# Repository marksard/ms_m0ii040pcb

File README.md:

# m0ii040 PCB

ms_m0ii040PCB is a dedicated PCB for m0ii040 produced by [yohewi](https://github.com/yohewi).  
This keyboard has two different PCBs with different layouts.  

# Completed example
Row staggered layout  

Treadstone layout  

# Layout
Row staggered layout  

Treadstone layout  

# Support software

QMK Firmware  
https://github.com/marksard/qmk_firmware/tree/own_build/keyboards/marksard/m0ii040pcb

# Build guide

https://github.com/marksard/ms_m0ii040pcb/blob/main/documentes/buildguide.md

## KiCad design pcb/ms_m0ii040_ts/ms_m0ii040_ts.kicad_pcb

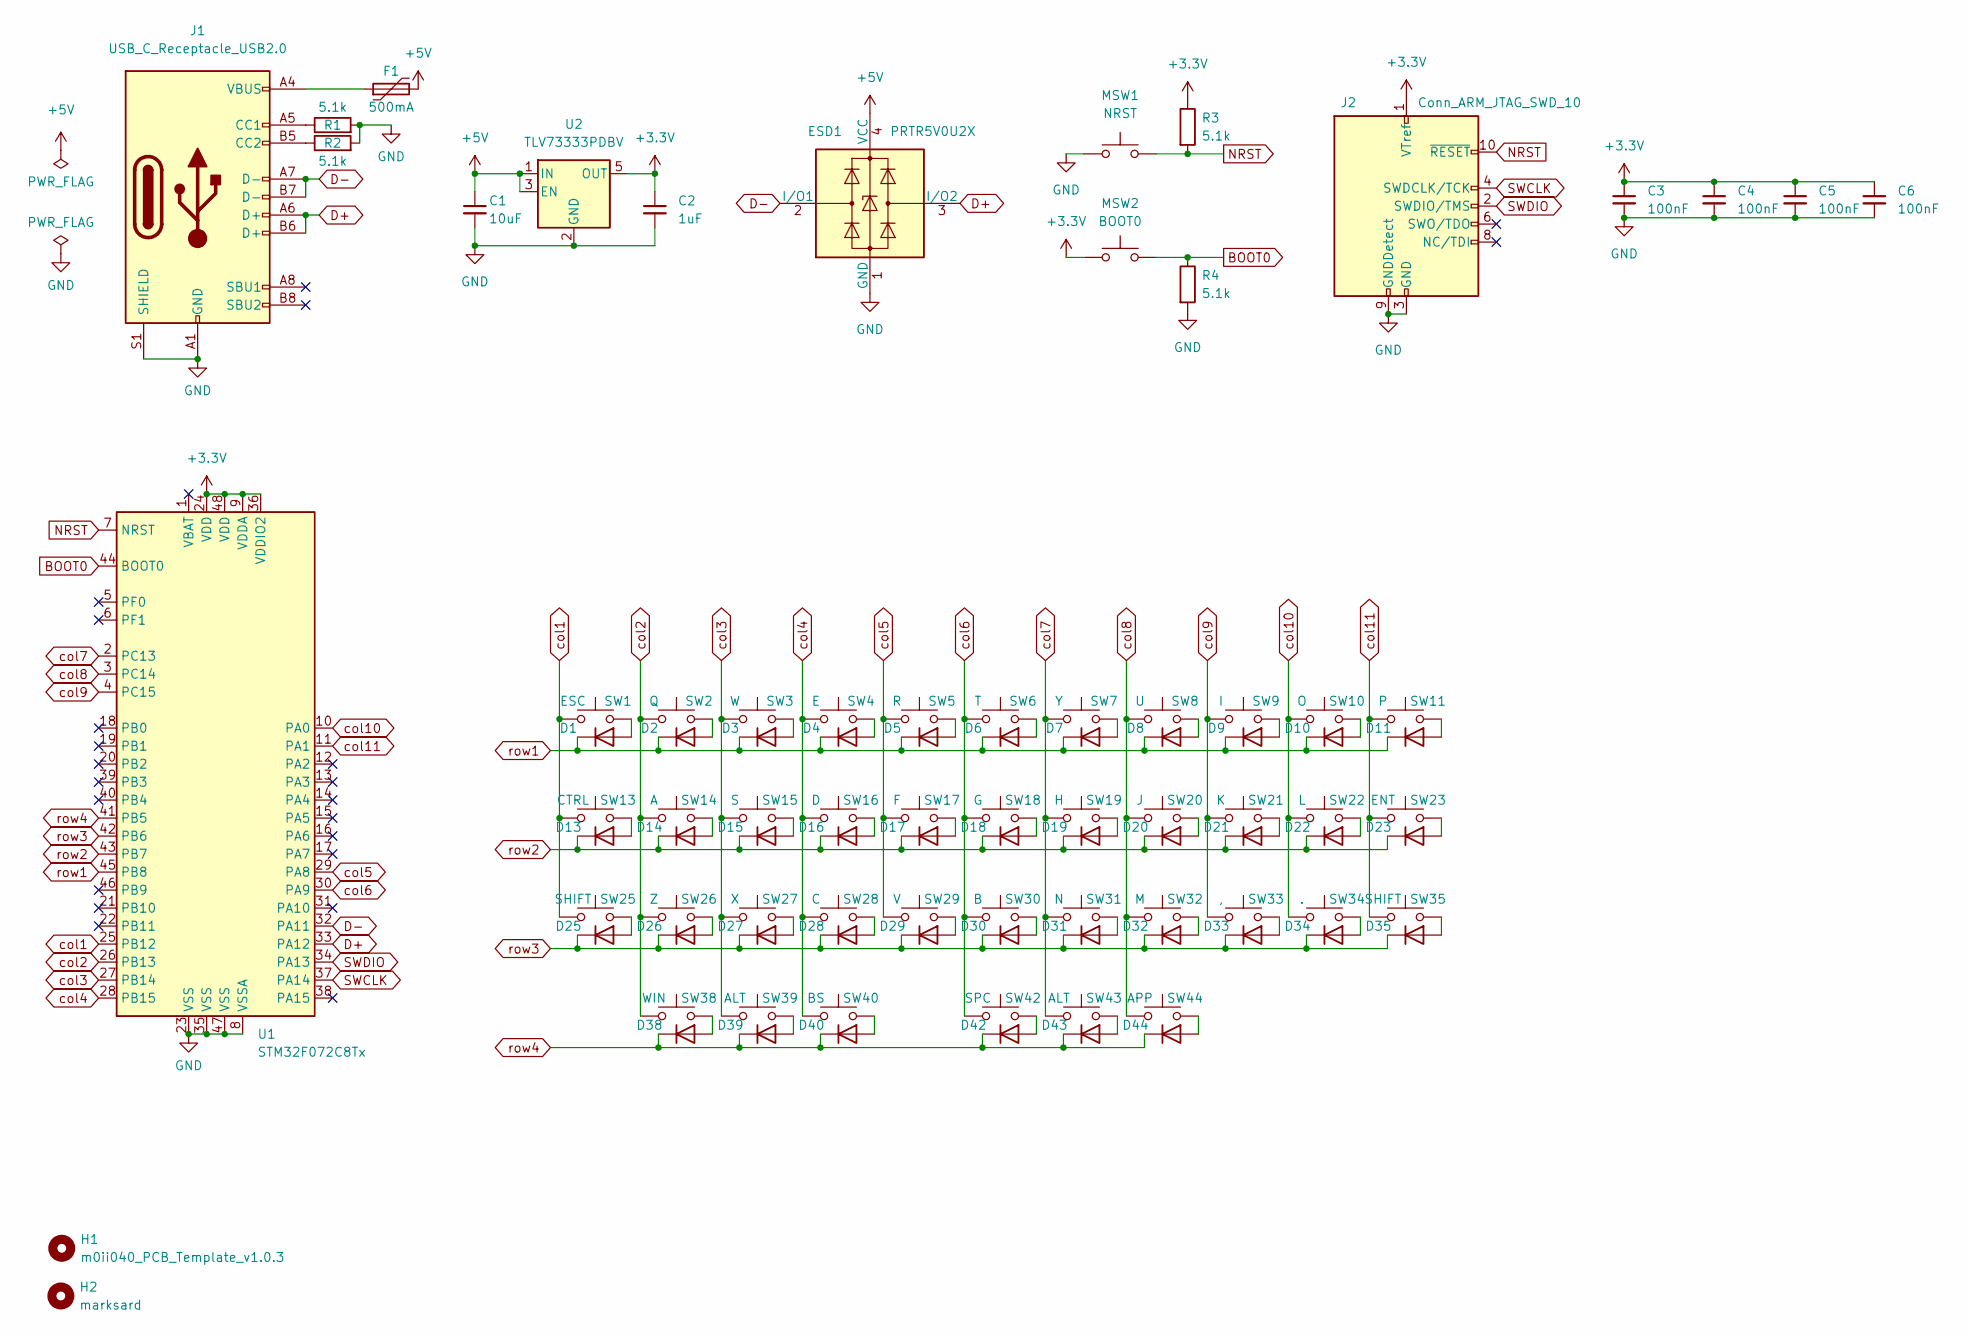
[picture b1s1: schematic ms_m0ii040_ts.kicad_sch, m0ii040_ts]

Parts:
C1: 10uF; C_0603_1608Metric
C2: 1uF; C_0402_1005Metric
C3, C4, C5, C6: 100nF; C_0402_1005Metric
D1, D2, D3, D4, D5, D6, D7, D8, D9, D10, D11, D13, D14, D15, D16, D17, D18, D19, D20, D21, D22, D23, D25, D26, D27, D28, D29, D30, D31, D32, D33, D34, D35, D38, D39, D40, D42, D43, D44: D; D_SOD-123; LCSC C81598
ESD1: PRTR5V0U2X; SOT-143; LCSC C12333
F1: 500mA; Fuse_0805_2012Metric; LCSC C261942
H1: m0ii040_PCB_Template_v1.0.3
H2: marksard; marksard_logo
J1: USB_C_Receptacle_USB2.0; HRO-TYPE-C-31-M-12-Assembly; LCSC C165948
J2: Conn_ARM_JTAG_SWD_10; PinHeader_2x06_P1.00mm_Vertical
MSW1: NRST; TVBP06-B043CB
MSW2: BOOT0; TVBP06-B043CB
R1, R2: 5.1k; R_0603_1608Metric
R3, R4: 5.1k; R_0402_1005Metric
SW1: ESC; MX-Hotswap-1U
SW2: Q; MX-Hotswap-1U
SW3: W; MX-Hotswap-1U
SW4: E; MX-Hotswap-1U
SW5: R; MX-Hotswap-1U
SW6: T; MX-Hotswap-1U
SW7: Y; MX-Hotswap-1U
SW8: U; MX-Hotswap-1U
SW9: I; MX-Hotswap-1U
SW10: O; MX-Hotswap-1U
SW11: P; MX-Hotswap-1U
SW13: CTRL; MX-Hotswap-1.25U
SW14: A; MX-Hotswap-1U
SW15: S; MX-Hotswap-1U
SW16: D; MX-Hotswap-1U
SW17: F; MX-Hotswap-1U
SW18: G; MX-Hotswap-1U
SW19: H; MX-Hotswap-1U
SW20: J; MX-Hotswap-1U
SW21: K; MX-Hotswap-1U
SW22: L; MX-Hotswap-1U
SW23: ENT; MX-Hotswap-1.75U
SW25: SHIFT; MX-Hotswap-1U
SW26: Z; MX-Hotswap-1U
SW27: X; MX-Hotswap-1U
SW28: C; MX-Hotswap-1U
SW29: V; MX-Hotswap-1U
SW30: B; MX-Hotswap-1U
SW31: N; MX-Hotswap-1U
SW32: M; MX-Hotswap-1U
SW33: ,; MX-Hotswap-1U
SW34: .; MX-Hotswap-1U
SW35: SHIFT; MX-Hotswap-1.5U
SW38: WIN; MX-Hotswap-1U
SW39, SW43: ALT; MX-Hotswap-1.25U
SW40: BS; MX-Hotswap-2.75U
SW42: SPC; MX-Hotswap-2.25U
SW44: APP; MX-Hotswap-1U
U1: STM32F072C8Tx; LQFP-48_7x7mm_P0.5mm; LCSC C80488
U2: TLV73333PDBV; SOT-23-5; LCSC C134139

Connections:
+3.3V: C2.1, C3.1, C4.1, C5.1, C6.1, J2.1 (VTref), MSW2.1, R3.1, U1.9 (VDDA), U1.24 (VDD), U1.36 (VDDIO2), U1.48 (VDD), U2.5 (OUT)
+5V: C1.1, ESD1.4 (VCC), F1.2, U2.1 (IN), U2.3 (EN)
BOOT0: MSW2.2, R4.1, U1.44 (BOOT0)
D+: ESD1.3 (I/O2), J1.A6 (D+), J1.B6 (D+), U1.33 (PA12)
D-: ESD1.2 (I/O1), J1.A7 (D-), J1.B7 (D-), U1.32 (PA11)
GND: C1.2, C2.2, C3.2, C4.2, C5.2, C6.2, ESD1.1 (GND), J1.A1 (GND), J1.A12 (GND), J1.B1 (GND), J1.B12 (GND), J1.S1 (SHIELD), J2.3 (GND), J2.5 (GND), J2.9 (GNDDetect), MSW1.1, R1.2, R2.2, R4.2, U1.8 (VSSA), U1.23 (VSS), U1.35 (VSS), U1.47 (VSS), U2.2 (GND)
NRST: J2.10 (~RESET), MSW1.2, R3.2, U1.7 (NRST)
unnamed: D1.2 (A), SW1.2
unnamed: D2.2 (A), SW2.2
unnamed: D3.2 (A), SW3.2
unnamed: D4.2 (A), SW4.2
unnamed: D5.2 (A), SW5.2
unnamed: D6.2 (A), SW6.2
unnamed: D7.2 (A), SW7.2
unnamed: D8.2 (A), SW8.2
unnamed: D9.2 (A), SW9.2
unnamed: D10.2 (A), SW10.2
unnamed: D11.2 (A), SW11.2
unnamed: D13.2 (A), SW13.2
unnamed: D14.2 (A), SW14.2
unnamed: D15.2 (A), SW15.2
unnamed: D16.2 (A), SW16.2
unnamed: D17.2 (A), SW17.2
unnamed: D18.2 (A), SW18.2
unnamed: D19.2 (A), SW19.2
unnamed: D20.2 (A), SW20.2
unnamed: D21.2 (A), SW21.2
unnamed: D22.2 (A), SW22.2
unnamed: D23.2 (A), SW23.2
unnamed: D25.2 (A), SW25.2
unnamed: D26.2 (A), SW26.2
unnamed: D27.2 (A), SW27.2
unnamed: D28.2 (A), SW28.2
unnamed: D29.2 (A), SW29.2
unnamed: D30.2 (A), SW30.2
unnamed: D31.2 (A), SW31.2
unnamed: D32.2 (A), SW32.2
unnamed: D33.2 (A), SW33.2
unnamed: D34.2 (A), SW34.2
unnamed: D35.2 (A), SW35.2
unnamed: D38.2 (A), SW38.2
unnamed: D39.2 (A), SW39.2
unnamed: D40.2 (A), SW40.2
unnamed: D42.2 (A), SW42.2
unnamed: D43.2 (A), SW43.2
unnamed: D44.2 (A), SW44.2
unnamed: F1.1, J1.A4 (VBUS), J1.A9 (VBUS), J1.B4 (VBUS), J1.B9 (VBUS)
unnamed: J1.A5 (CC1), R1.1
unnamed: J1.B5 (CC2), R2.1
SWCLK: J2.4 (SWDCLK/TCK), U1.37 (PA14)
SWDIO: J2.2 (SWDIO/TMS), U1.34 (PA13)
col1: SW1.1, SW13.1, SW25.1, U1.25 (PB12)
col2: SW2.1, SW14.1, SW26.1, SW38.1, U1.26 (PB13)
col3: SW3.1, SW15.1, SW27.1, SW39.1, U1.27 (PB14)
col4: SW4.1, SW16.1, SW28.1, SW40.1, U1.28 (PB15)
col5: SW5.1, SW17.1, SW29.1, U1.29 (PA8)
col6: SW6.1, SW18.1, SW30.1, SW42.1, U1.30 (PA9)
col7: SW7.1, SW19.1, SW31.1, SW43.1, U1.2 (PC13)
col8: SW8.1, SW20.1, SW32.1, SW44.1, U1.3 (PC14)
col9: SW9.1, SW21.1, SW33.1, U1.4 (PC15)
col10: SW10.1, SW22.1, SW34.1, U1.10 (PA0)
col11: SW11.1, SW23.1, SW35.1, U1.11 (PA1)
row1: D1.1 (K), D2.1 (K), D3.1 (K), D4.1 (K), D5.1 (K), D6.1 (K), D7.1 (K), D8.1 (K), D9.1 (K), D10.1 (K), D11.1 (K), U1.45 (PB8)
row2: D13.1 (K), D14.1 (K), D15.1 (K), D16.1 (K), D17.1 (K), D18.1 (K), D19.1 (K), D20.1 (K), D21.1 (K), D22.1 (K), D23.1 (K), U1.43 (PB7)
row3: D25.1 (K), D26.1 (K), D27.1 (K), D28.1 (K), D29.1 (K), D30.1 (K), D31.1 (K), D32.1 (K), D33.1 (K), D34.1 (K), D35.1 (K), U1.42 (PB6)
row4: D38.1 (K), D39.1 (K), D40.1 (K), D42.1 (K), D43.1 (K), D44.1 (K), U1.41 (PB5)

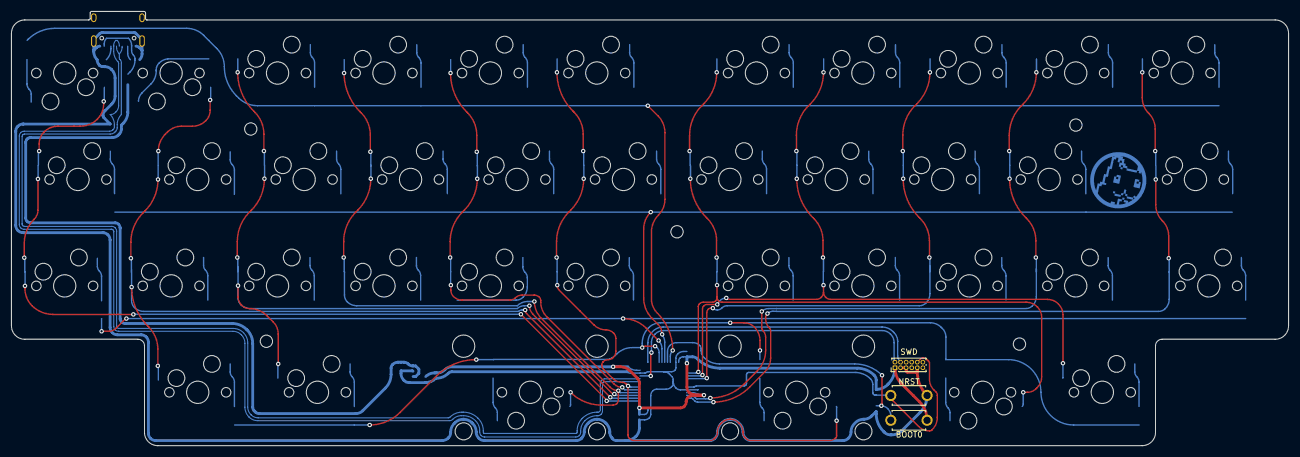
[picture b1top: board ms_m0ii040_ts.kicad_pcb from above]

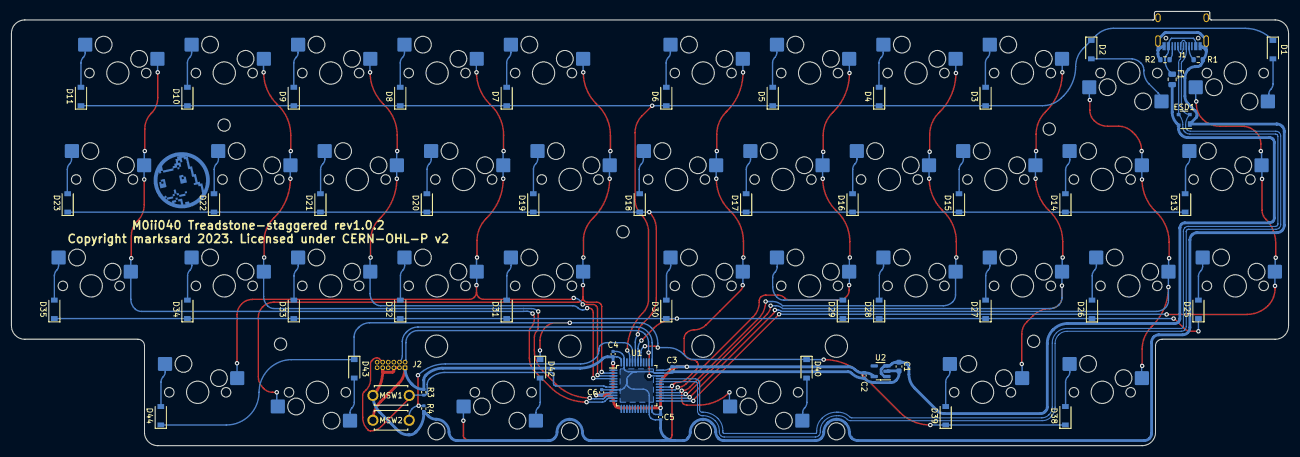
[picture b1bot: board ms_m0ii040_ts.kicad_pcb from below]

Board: 2 copper layers, 228.6 x 77.7 mm, 98 parts (57 on the bottom side), 66 nets.

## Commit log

2023-03-07 add pcb and license
2023-03-20 add ts layout pcb
2023-03-20 create buildguide
2023-03-21 D- and GND slightly separated.

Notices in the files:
pcb/ms_m0ii040_ts/ms_m0ii040_ts.kicad_pcb:
Copyright marksard 2023. Licensed under CERN-OHL-P v2
